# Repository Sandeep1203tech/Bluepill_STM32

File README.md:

# Bluepill_STM32
 STM32 Microcontroller based USB PCB designing.

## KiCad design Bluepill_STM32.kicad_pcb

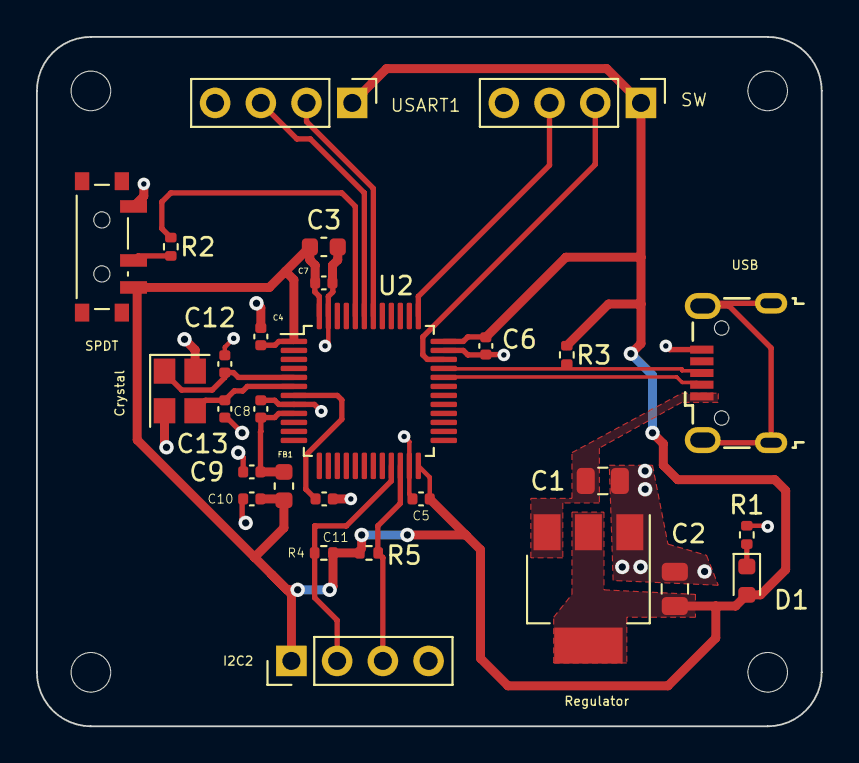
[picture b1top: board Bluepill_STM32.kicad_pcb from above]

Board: 2 copper layers, 43.6 x 38.3 mm, 32 parts (0 on the bottom side), 18 nets.

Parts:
C1, C2: 20u; C_0805_2012Metric
C3: 10u; C_0603_1608Metric
C4, C5, C6, C7, C11: 100n; C_0402_1005Metric
C8: 10n; C_0402_1005Metric
C9, C10: 1u; C_0402_1005Metric
C12, C13: 10p; C_0402_1005Metric
Crystal: 16MHz; Crystal_SMD_3225-4Pin_3.2x2.5mm
D1: RED; LED_0603_1608Metric
FB1: 120R; L_0603_1608Metric
H1, H2, H3, H4: MountingHole; MountingHole_2.2mm_M2
I2C2: Conn_01x04_Male; PinHeader_1x04_P2.54mm_Vertical
R1, R3, R4, R5: 1.5; R_0402_1005Metric
R2: 10k; R_0402_1005Metric
Regulator: AMS1117-3.3; SOT-223-3_TabPin2
SPDT: SW_SPDT; SW_SPDT_PCM12
SW: Conn_01x04_Male; PinHeader_1x04_P2.54mm_Vertical
U2: STM32F103C8T6; LQFP-48_7x7mm_P0.5mm
USART1: Conn_01x04_Male; PinHeader_1x04_P2.54mm_Vertical
USB: USB_B_Micro; USB_Micro-B_Wuerth_629105150521

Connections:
+3.3V: C2.1, C3.1, C4.1, C5.1, C6.1, C7.1, C10.1, D1.2 (A), FB1.1, I2C2.1, R3.1, R4.1, R5.1, Regulator.2 (VO), SPDT.3 (C), SW.1, U2.1 (VBAT), U2.24 (VDD), U2.36 (VDD), U2.48 (VDD), USART1.1
+3.3VA: C8.1, C9.1, FB1.2, U2.9 (VDDA)
/BOOT0: R2.2, U2.44 (BOOT0)
/HSE_IN: C12.1, Crystal.1, U2.5 (PD0)
/HSE_OUT: C13.1, Crystal.3, U2.6 (PD1)
/I2C2_SCL: I2C2.2, R4.2, U2.21 (PB10)
/I2C2_SDA: I2C2.3, R5.2, U2.22 (PB11)
/NRST: C11.1, U2.7 (NRST)
/SWCLK: SW.3, U2.37 (PA14)
/SWDIO: SW.2, U2.34 (PA13)
/SWITCH_BOOT0: R2.1, SPDT.2 (B)
/USART1_TX: U2.42 (PB6), USART1.2
/USARTI_RX: U2.43 (PB7), USART1.3
/USB_D+: R3.2, U2.33 (PA12), USB.3 (D+)
/USB_D-: U2.32 (PA11), USB.2 (D-)
/power led cathode: D1.1 (K), R1.1
GND: C1.2, C2.2, C3.2, C4.2, C5.2, C6.2, C7.2, C8.2, C9.2, C10.2, C11.2, C12.2, C13.2, Crystal.2, Crystal.4, I2C2.4, R1.2, Regulator.1 (GND), SPDT.1 (A), SW.4, U2.8 (VSSA), U2.23 (VSS), U2.35 (VSS), U2.47 (VSS), USART1.4, USB.5 (GND)
VBUS: C1.1, Regulator.3 (VI), USB.1 (VBUS)
